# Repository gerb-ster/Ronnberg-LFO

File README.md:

# Ronnberg LFO

This is my take on the LFO module designed by Niklas Ronnberg. I’ve changed the range switch with an on-off-on type switch. This way, in the off position, the timing cap consist of a single .001 uF cap, the other 2 positions either add an extra .068uF or 1uF cap. This increases the selectable range quit a bit. I’ve also added a triangle-to-sine converter based on a design by Thomas Henry.

## Status: Finished

- done: first schematic & board design
- done: breadboard and test
- done: design frontpanel
- done: order PCB and build prototype

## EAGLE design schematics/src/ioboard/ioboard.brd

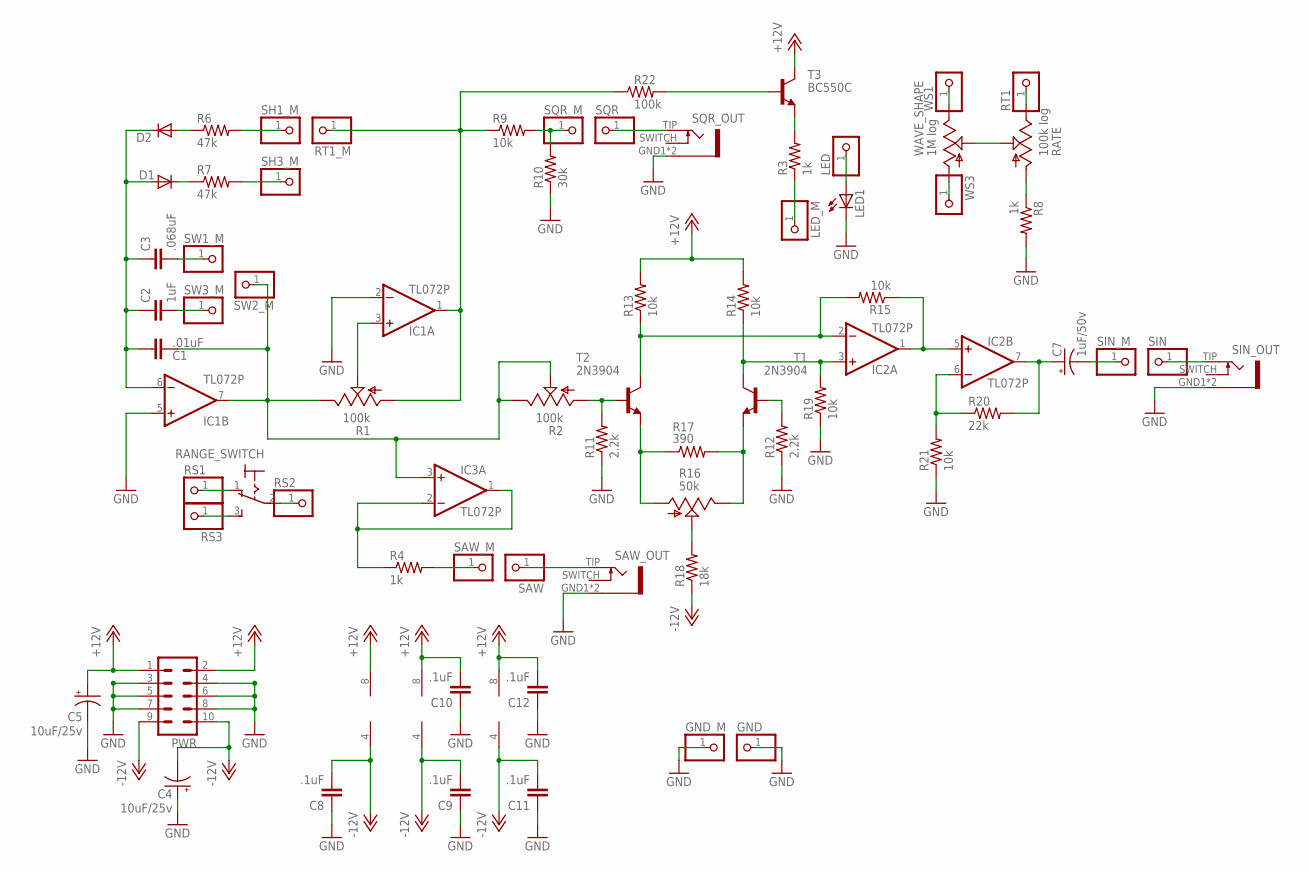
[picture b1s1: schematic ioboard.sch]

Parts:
C1: .01uF; C050-025X075
C2: 1uF; C050-025X075
C3: .068uF; C050-025X075
C4, C5: 10uF/25v; E2,5-5
C7: 1uF/50v; E2,5-5
C8, C9, C10, C11, C12: .1uF; C025-024X044
D1, D2: 1N4148DO35-7; DO35-7
GND: PINHD-1X1; 1X01
GND_M: PINHD-1X1; 1X01
IC1, IC2, IC3: TL072P; DIL08
LED: PINHD-1X1; 1X01
LED1: LED5MM
LED_M: PINHD-1X1; 1X01
PWR: ML10
R1, R2: 100k; RJ9W
R3, R8: 1k; 0207/10
R4: 1k; 0207/2V
R6, R7: 47k; 0207/10
R9, R13: 10k; 0207/10
R10: 30k; 0207/10
R11, R12: 2.2k; 0207/10
R14, R15, R19, R21: 10k; 0207/2V
R16: 50k; RJ9W
R17: 390; 0207/10
R18: 18k; 0207/10
R20: 22k; 0207/2V
R22: 100k; 0207/10
RANGE_SWITCH: M9040P
RATE: 100k log; EVUF
RS1, RS2, RS3: PINHD-1X1; 1X01
RT1, RT1_M: PINHD-1X1; 1X01
SAW: PINHD-1X1; 1X01
SAW_M: PINHD-1X1; 1X01
SAW_OUT: PJ301BMPJ301BM; PJ301BM
SH1_M, SH3_M: PINHD-1X1; 1X01
SIN: PINHD-1X1; 1X01
SIN_M: PINHD-1X1; 1X01
SIN_OUT: PJ301BMPJ301BM; PJ301BM
SQR: PINHD-1X1; 1X01
SQR_M: PINHD-1X1; 1X01
SQR_OUT: PJ301BMPJ301BM; PJ301BM
SW1_M, SW2_M, SW3_M: PINHD-1X1; 1X01
T1, T2: 2N3904; TO92
T3: BC550C; TO92-CBE
WAVE_SHAPE: 1M log; EVUF
WS1, WS3: PINHD-1X1; 1X01

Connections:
+12V: C5.+, C10.2, C12.2, IC1.8 (V+), IC2.8 (V+), IC3.8 (V+), PWR.1, PWR.2, R13.2, R14.2, T3.C
-12V: C4.-, C8.2, C9.2, C11.2, IC1.4 (V-), IC2.4 (V-), IC3.4 (V-), PWR.9, PWR.10, R18.1
GND: C4.+, C5.-, C8.1, C9.1, C10.1, C11.1, C12.1, GND.1, GND_M.1, IC1.2 (-IN), IC1.5 (+IN), LED1.K (C), PWR.3, PWR.4, PWR.5, PWR.6, PWR.7, PWR.8, R8.2, R10.1, R11.1, R12.1, R19.1, R21.1, SAW_OUT.GND1 (5), SAW_OUT.GND2 (5), SIN_OUT.GND1 (5), SIN_OUT.GND2 (5), SQR_OUT.GND1 (5), SQR_OUT.GND2 (5)
unnamed: RATE.2 (S), WAVE_SHAPE.2 (S)
unnamed: D2.A, R6.1
unnamed: D1.C, R7.1
unnamed: RATE.3 (E), RT1.1
unnamed: R7.2, SH3_M.1
unnamed: C1.1, C2.1, C3.1, D1.A, D2.C, IC1.6 (-IN)
unnamed: C2.2, SW3_M.1
unnamed: R8.1, RATE.1 (A)
unnamed: RANGE_SWITCH.2, RS2.1
unnamed: IC1.3 (+IN), R1.S
unnamed: LED_M.1, R3.1
unnamed: IC1.1 (OUT), R1.A, R9.1, R22.1, RT1_M.1
unnamed: IC2.2 (-IN), R13.1, R15.2, T2.1 (C)
unnamed: C1.2, IC1.7 (OUT), IC3.3 (+IN), R1.E, R2.E, R2.S, SW2_M.1
unnamed: R22.2, T3.B
unnamed: R9.2, R10.2, SQR_M.1
unnamed: R16.S, R18.2
unnamed: C7.+, IC2.7 (OUT), R20.2
unnamed: C7.-, SIN_M.1
unnamed: R2.A, R11.2, T2.2 (B)
unnamed: R16.A, R17.1, T2.3 (E)
unnamed: R16.E, R17.2, T1.3 (E)
unnamed: LED.1, LED1.A
unnamed: R3.2, T3.E
unnamed: R12.2, T1.2 (B)
unnamed: IC2.3 (+IN), R14.1, R19.2, T1.1 (C)
unnamed: IC2.1 (OUT), IC2.5 (+IN), R15.1
unnamed: IC2.6 (-IN), R20.1, R21.2
unnamed: SAW.1, SAW_OUT.TIP (3)
unnamed: SQR.1, SQR_OUT.TIP (3)
unnamed: SIN.1, SIN_OUT.TIP (3)
unnamed: WAVE_SHAPE.3 (E), WS1.1
unnamed: RANGE_SWITCH.3 (S), RS3.1
unnamed: C3.2, SW1_M.1
unnamed: IC3.1 (OUT), IC3.2 (-IN), R4.1
unnamed: WAVE_SHAPE.1 (A), WS3.1
unnamed: R4.2, SAW_M.1
SH1_M: R6.2, SH1_M.1
SLOW_IO: RANGE_SWITCH.1 (O), RS1.1

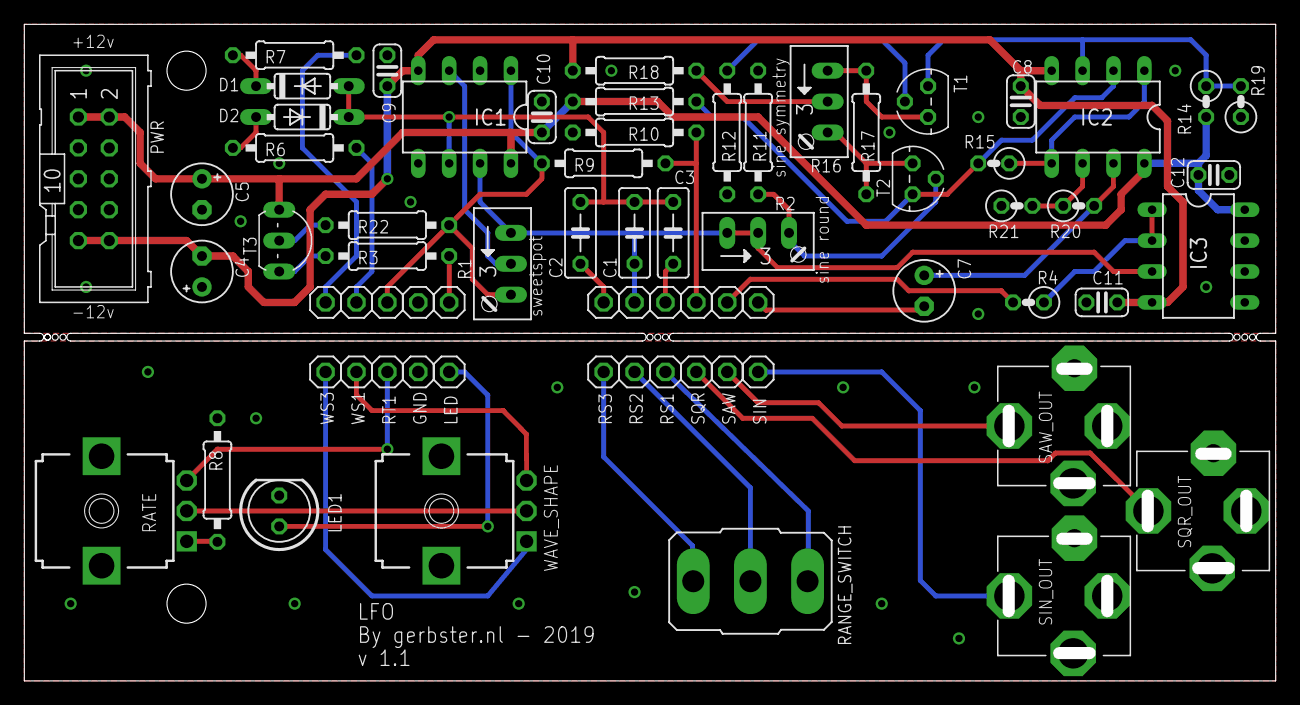
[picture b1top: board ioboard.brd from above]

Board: 2 copper layers, 101.9 x 53.0 mm, 70 parts (0 on the bottom side), 42 nets.

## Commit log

2021-05-06 some files
2021-05-06 fixed gitignore
2021-05-07 Added files & structure
2021-05-10 Added Status
2021-05-11 Added Status & Images
2021-08-06 Updated some schematics and docs
2021-08-10 Fixed some bugs and updated documentation
2022-04-20 Some updates & bugfixes
2022-04-22 Fixed schematics & descriptions
2022-05-17 Updated Firmware
2022-05-18 Updated Faceplates
2022-05-18 Fixed issues
2022-05-21 Fixed schematics
2022-05-28 General updates
2022-06-20 Updated schematics with missing values
